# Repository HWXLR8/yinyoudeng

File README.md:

# 音游灯

This is an RGB LED for use with Sanwa rhythm game buttons (also compaitible with many chinese clone buttons). Intended to be soldered to those cheap WS2812 circular PCBs readily available on Aliexpress which include on-board current limiting resistors and decoupling caps:

BOM:
```
1 ATTINY13A-SSU
1 100nF SMD cap 0805
1 schottky diode (MFG# UPS115UE3)
1 4x4x1.5mm tactile SMD tactile push button
1 WS2812 LED on PCB with res+cap
```
PCBs should be manufactured at 2.0mm thickness instead of standard 1.6mm. Soldering the WS2812 module on to the PCB can be a bit tricky, so I designed a jig which simplifies the alignment of the parts. The model is available in `jig/jig.stl`.

Special thanks to Tim (cpldcpu) for the <a href="https://github.com/cpldcpu/light_ws2812">implementation of
the WS2812 protocol</a>.

享受音游 享受生活

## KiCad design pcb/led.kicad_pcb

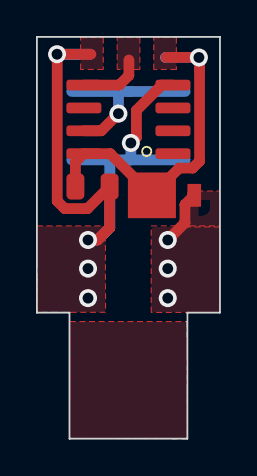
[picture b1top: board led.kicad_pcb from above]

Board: 2 copper layers, 10.2 x 22.3 mm, 4 parts (1 on the bottom side), 3 nets.

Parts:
C1: 100nF; C_0805_2012Metric
D2: D_Schottky; D_Powermite_AK
SW1: SW_Push; SW_SPST_TL3342
U1: ATtiny13A-SS; SOIC-8_3.9x4.9mm_P1.27mm

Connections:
GND: C1.2, SW1.2, U1.4 (GND)
unnamed: C1.1, D2.1 (K), U1.8 (VCC)
unnamed: SW1.1, U1.7 (PB2)

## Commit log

2023-05-28 init
2023-08-07 add PCB thickness disclaimer to README
2024-01-14 add LICENSE
2025-08-16 add jig for soldering alignement
2025-08-17 [fw] simplify color table, make debounce more robust
2025-08-17 [fw] simplify build system
